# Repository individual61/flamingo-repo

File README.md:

FLAMINGO!

My festival buddy.My fave programs are the damped harmonic oscillator, the bouncing ball, and green fire. 

First iteration was a perfboard mess, second was a custom PCBA I designed and assembled. Currently runs off a small, flat USB power bank.

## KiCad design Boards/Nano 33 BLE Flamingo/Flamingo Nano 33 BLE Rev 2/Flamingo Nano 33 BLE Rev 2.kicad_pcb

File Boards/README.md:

This directory contains the board files.

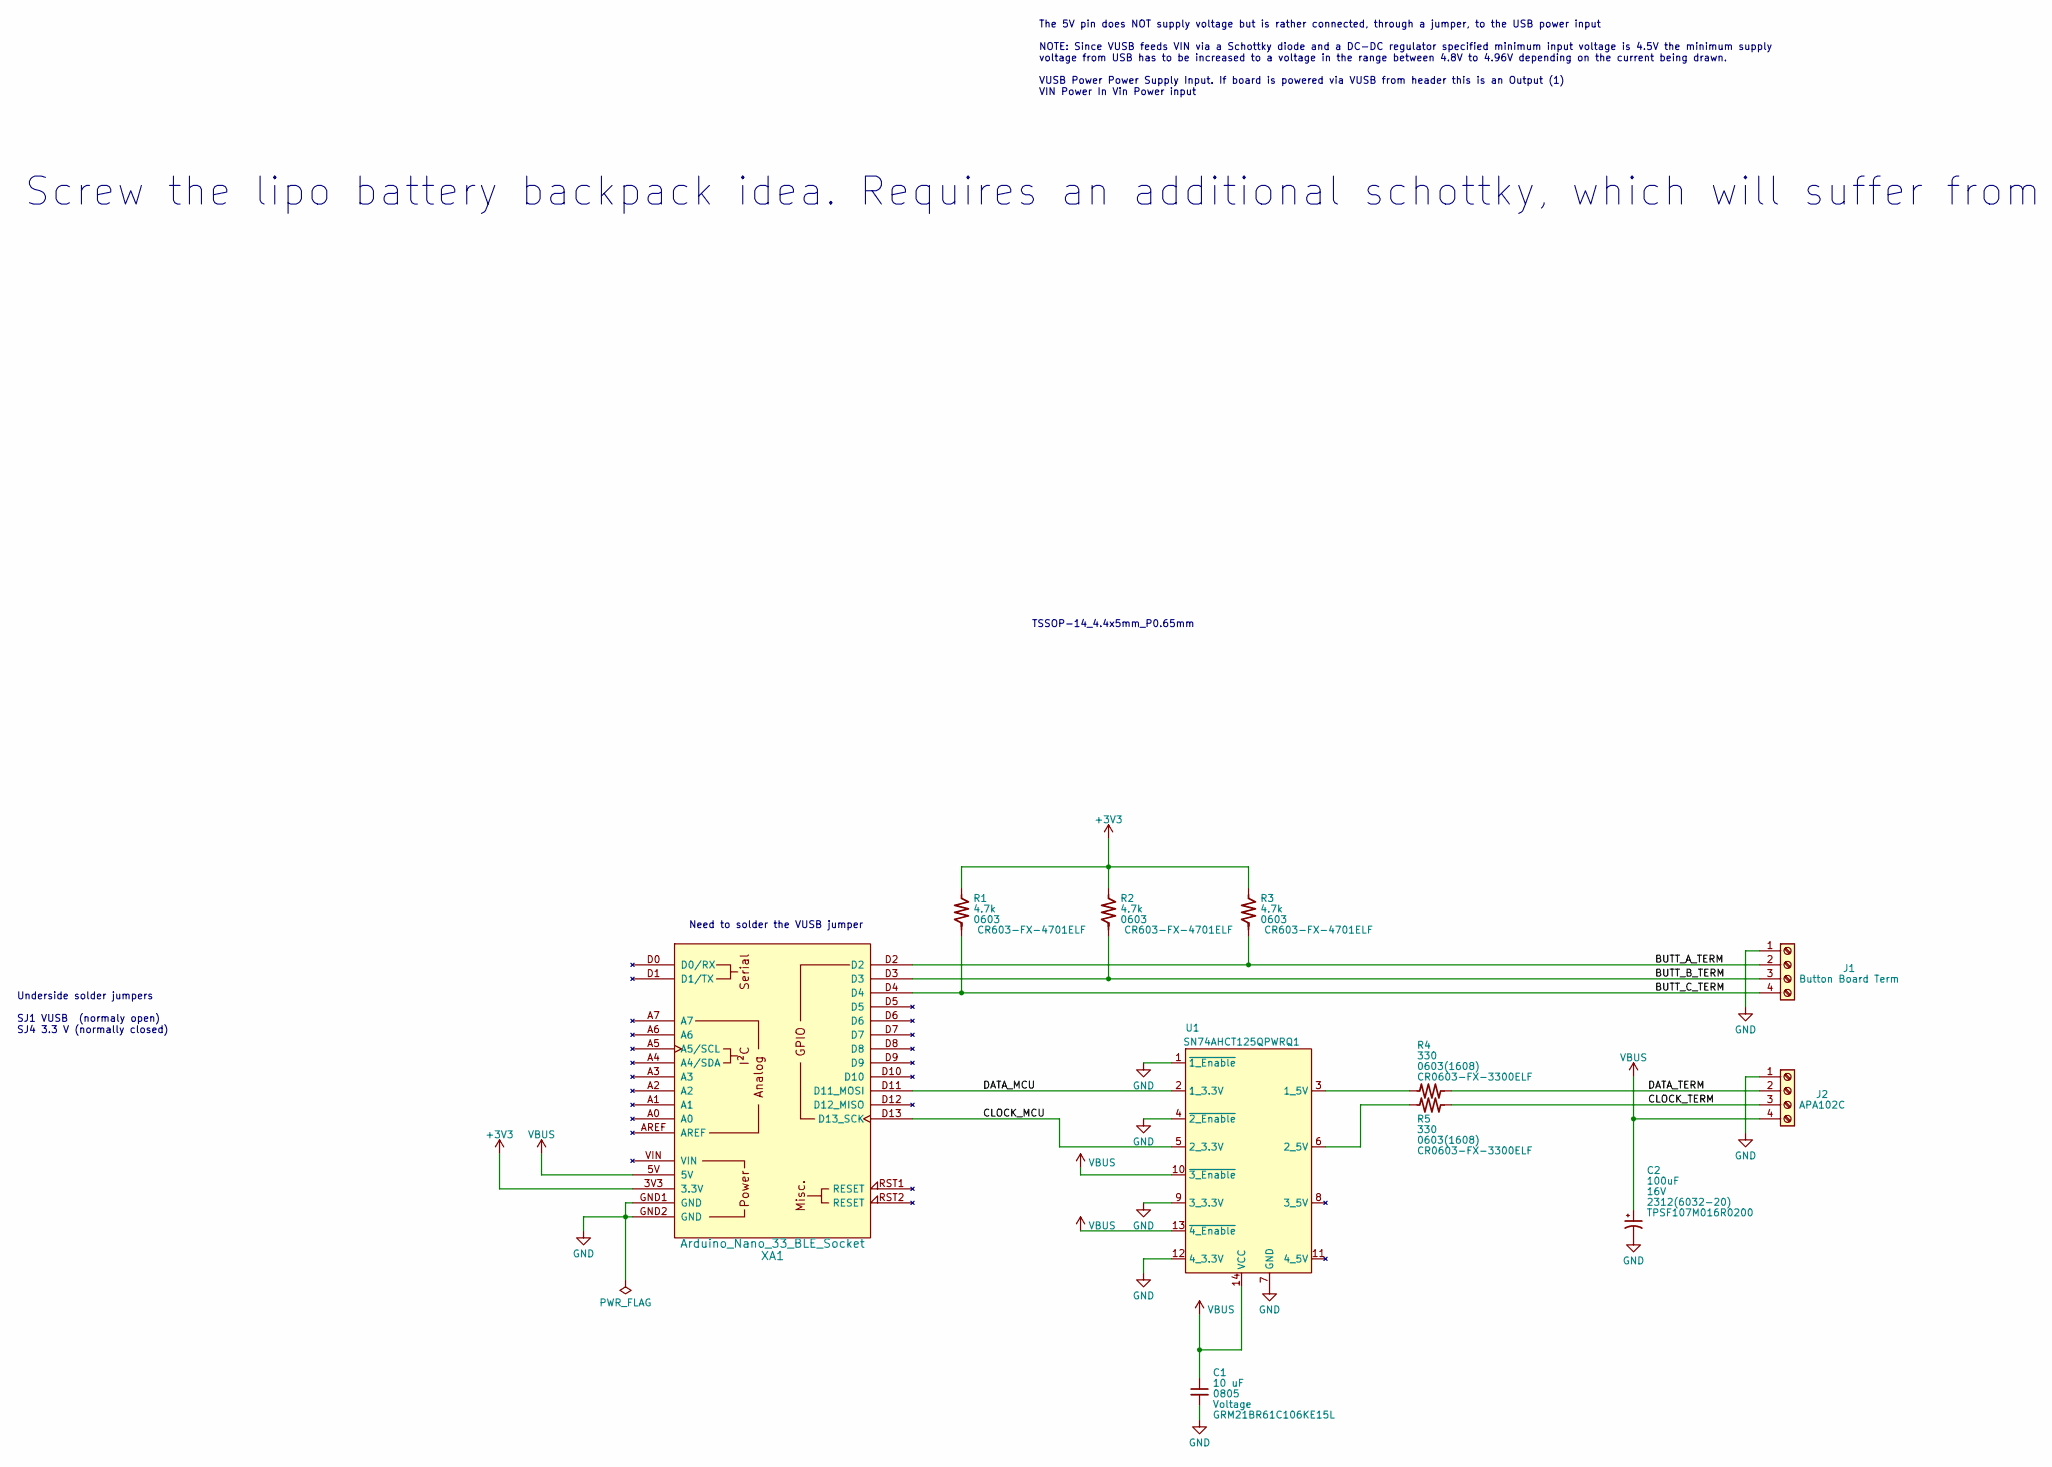
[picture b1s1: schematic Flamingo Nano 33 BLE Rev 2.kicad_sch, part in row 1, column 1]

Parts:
C1: 10 uF; C_0805_2012Metric_Pad1.18x1.45mm_HandSolder; Voltage Rating Voltage; MPN GRM21BR61C106KE15L
C2: 100uF; CP_EIA-6032-20_AVX-F_Pad2.25x2.35mm_HandSolder; Voltage Rating 16V; MFR P/N TPSF107M016R0200
J1: Button Board Term; TerminalBlock_TE_282834-4_1x04_P2.54mm_Horizontal; MFR PN 282834-4; DIGIKEY PN A98335-ND
J2: APA102C; TerminalBlock_TE_282834-4_1x04_P2.54mm_Horizontal; MFR PN 282834-4; DIGIKEY PN A98335-ND
R1, R2, R3: 4.7k; R_0603_1608Metric_Pad0.98x0.95mm_HandSolder; MPN CR603-FX-4701ELF; Digi-Key_PN 455-1719-ND
R4, R5: 330; R_0603_1608Metric_Pad0.98x0.95mm_HandSolder; MPN CR0603-FX-3300ELF
U1: SN74AHCT125QPWRQ1; TSSOP-14_4.4x5mm_P0.65mm
XA1: Arduino_Nano_33_BLE_Socket; Arduino_Nano_Every_Socket

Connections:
+3V3: R1.1, R2.1, R3.1, XA1.3V3 (3.3V)
/BUTT_A_TERM: J1.2, R3.2, XA1.D2
/BUTT_B_TERM: J1.3, R2.2, XA1.D3
/BUTT_C_TERM: J1.4, R1.2, XA1.D4
/CLOCK_MCU: U1.5 (2_3.3V), XA1.D13 (D13_SCK)
/CLOCK_TERM: J2.3, R5.2
/DATA_MCU: U1.2 (1_3.3V), XA1.D11 (D11_MOSI)
/DATA_TERM: J2.2, R4.2
GND: C1.2, C2.2, J1.1, J2.1, U1.1 (~1_Enable), U1.4 (~2_Enable), U1.7 (GND), U1.9 (3_3.3V), U1.12 (4_3.3V), XA1.GND1 (GND), XA1.GND2 (GND)
unnamed: R4.1, U1.3 (1_5V)
unnamed: R5.1, U1.6 (2_5V)
VBUS: C1.1, C2.1, J2.4, U1.10 (~3_Enable), U1.13 (~4_Enable), U1.14 (VCC), XA1.5V

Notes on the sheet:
Underside solder jumpers SJ1 VUSB (normaly open) SJ4 3.3 V (normally closed)
Screw the lipo battery backpack idea. Requires an additional schottky, which will suffer from Vf drop when running lights. Just use a USB power bank.
TSSOP-14_4.4x5mm_P0.65mm
The 5V pin does NOT supply voltage but is rather connected, through a jumper, to the USB power input NOTE: Since VUSB feeds VIN via a Schottky diode and a DC-DC regulator specified minimum input voltage is 4.5V the minimum supply voltage from USB has to be increased to a voltage in the range betwee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
Need to solder the VUSB jumper

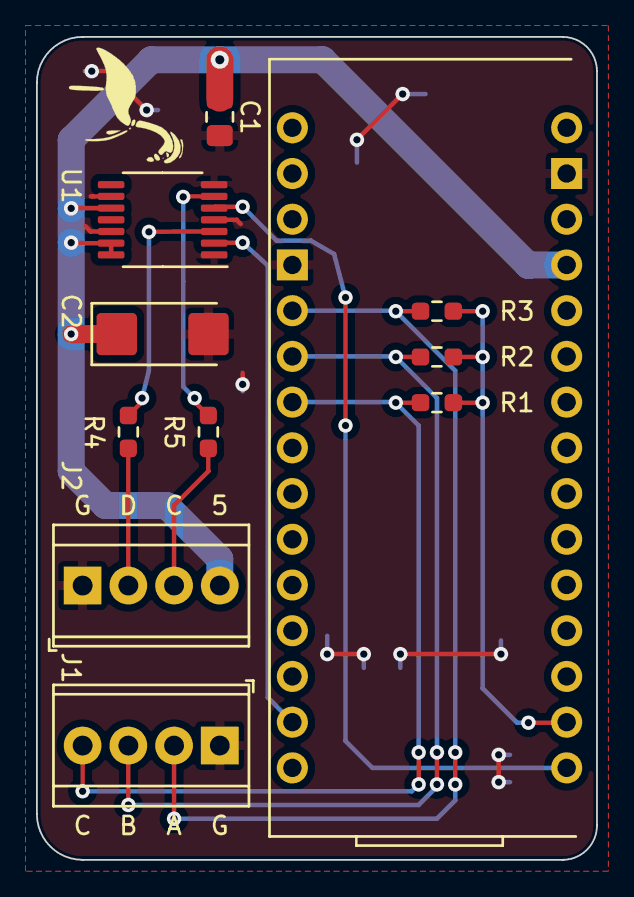
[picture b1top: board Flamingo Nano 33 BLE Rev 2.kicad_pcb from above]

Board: 2 copper layers, 31.1 x 45.7 mm, 11 parts (0 on the bottom side), 12 nets.

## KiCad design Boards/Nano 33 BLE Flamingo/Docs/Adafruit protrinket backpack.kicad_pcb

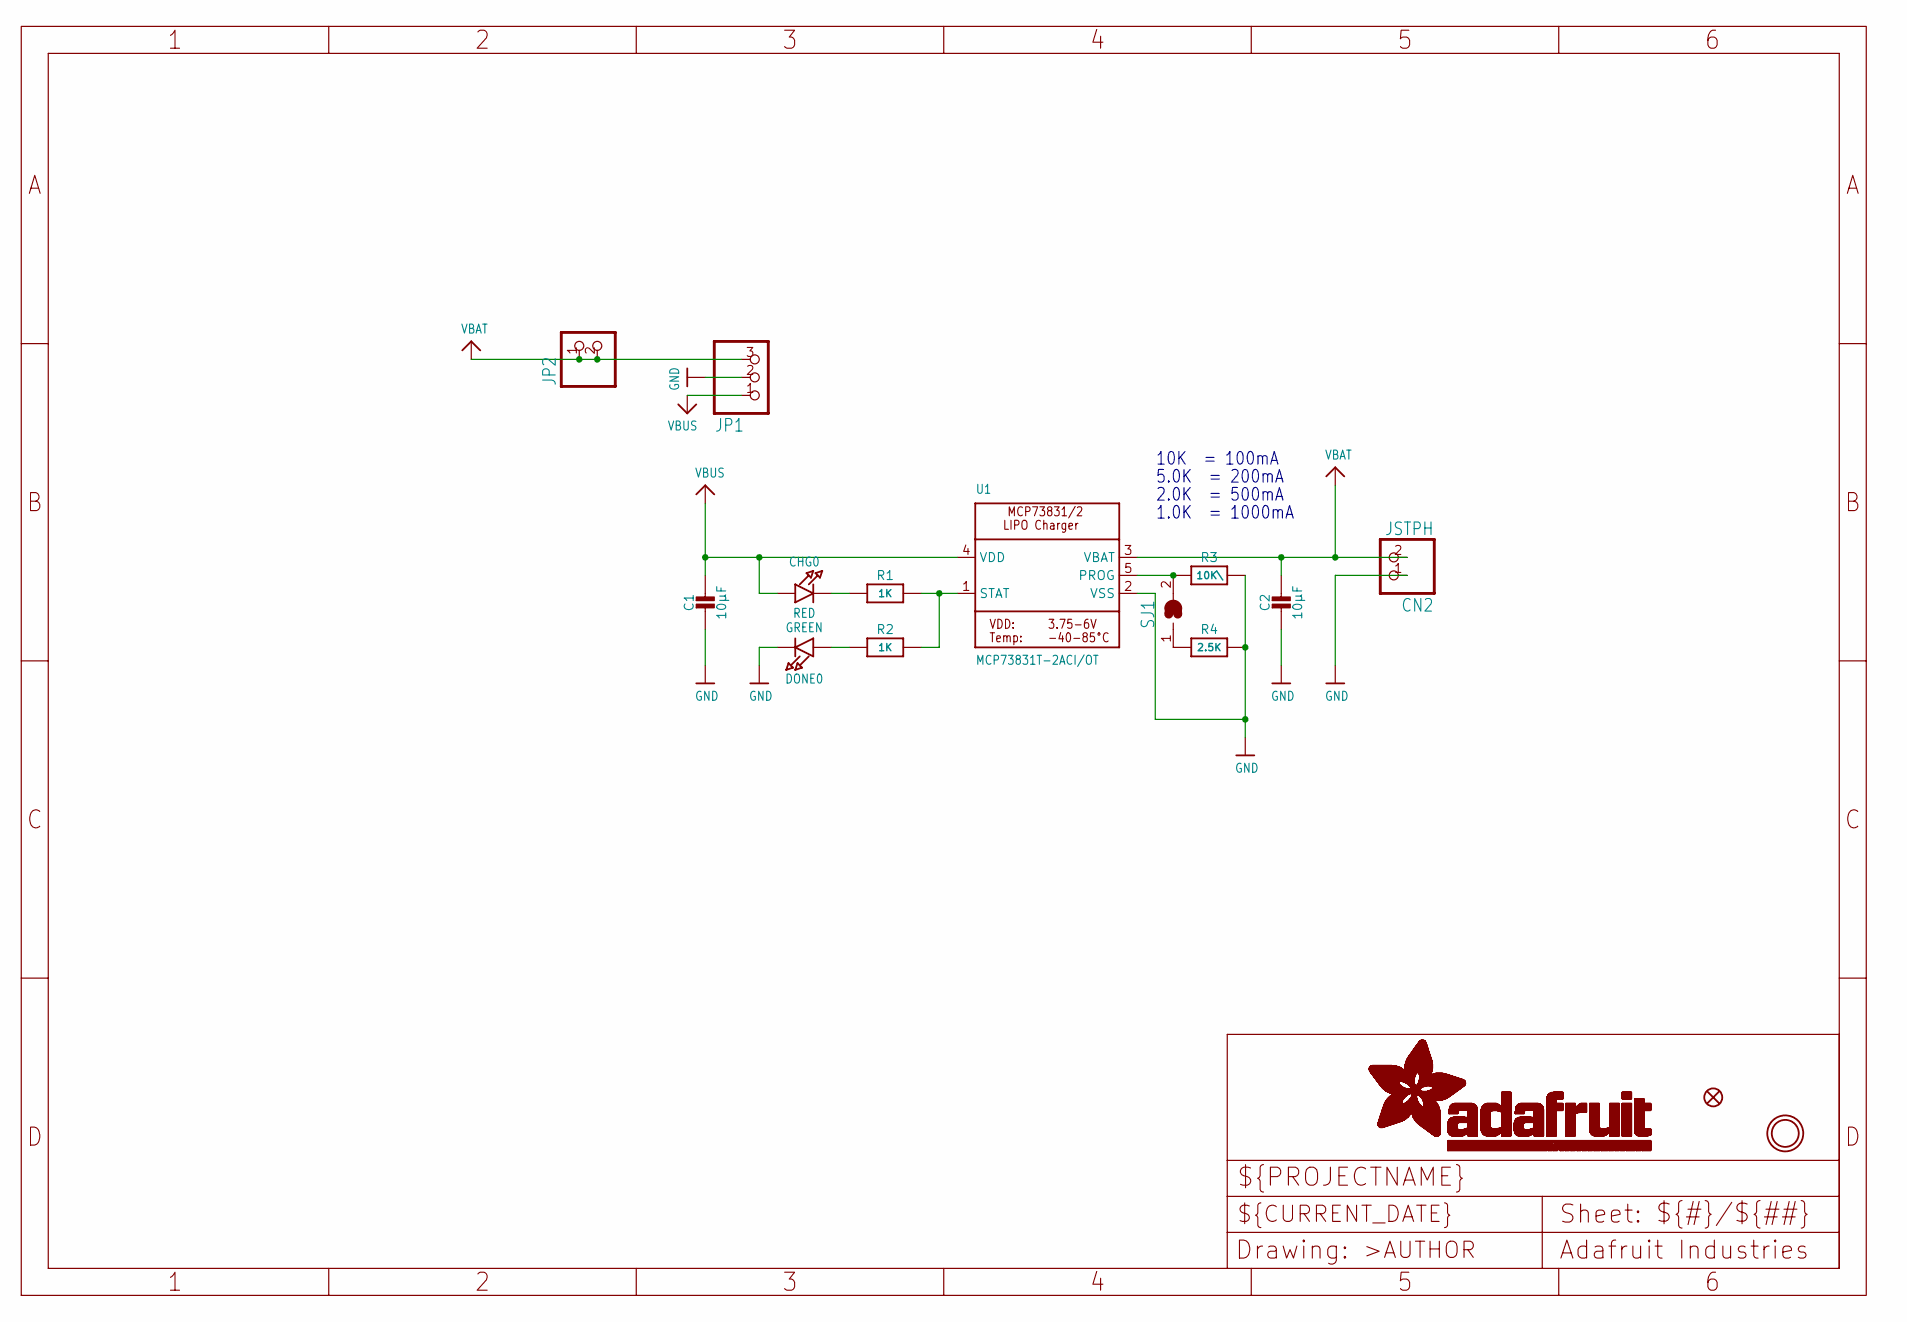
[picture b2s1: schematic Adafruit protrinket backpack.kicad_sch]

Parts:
C1, C2: 10µF; 0805-NO
CHG0: RED; CHIPLED_0805_NOOUTLINE
CN2: JSTPH; JSTPH2
DONE0: GREEN; CHIPLED_0805_NOOUTLINE
FID1: FIDUCIAL""; FIDUCIAL_1MM
JP1: HEADER-1X376MIL; 1X03_ROUND_76
JP2: HEADER-1X2ROUND; 1X02_ROUND
R1, R2: 1K; 0805-NO
R3: 10K\; _0805MP
R4: 2.5K; 0805-NO
SJ1: SOLDERJUMPER; SOLDERJUMPER_ARROW_NOPASTE
U1: MCP73831T-2ACI/OT; SOT23-5
U$10: MOUNTINGHOLE2.5; MOUNTINGHOLE_2.5_PLATED

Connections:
GND: C1.2, C2.2, CN2.1, DONE0.C, JP1.2, R3.2, R4.2, U1.2 (VSS)
unnamed: CHG0.C, R1.1
unnamed: R1.2, R2.2, U1.1 (STAT)
unnamed: R4.1, SJ1.1
unnamed: R3.1, SJ1.2, U1.5 (PROG)
unnamed: DONE0.A, R2.1
VBAT: C2.1, CN2.2, JP1.3, JP2.1, JP2.2, U1.3 (VBAT)
VBUS: C1.1, CHG0.A, JP1.1, U1.4 (VDD)

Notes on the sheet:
10K = 100mA
5.0K = 200mA
2.0K = 500mA
1.0K = 1000mA

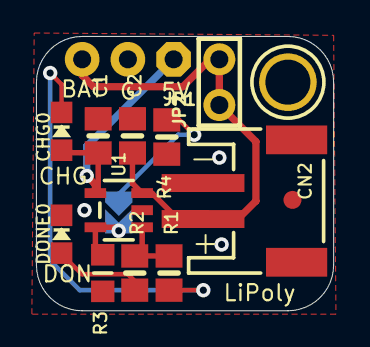
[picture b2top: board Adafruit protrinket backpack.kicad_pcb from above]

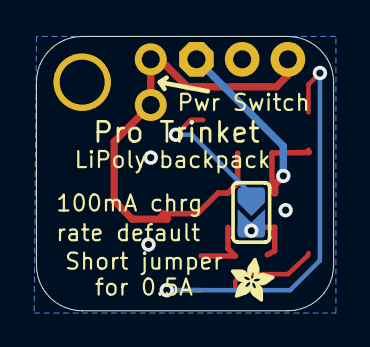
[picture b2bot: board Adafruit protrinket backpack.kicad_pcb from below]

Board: 2 copper layers, 16.5 x 15.2 mm, 16 parts (2 on the bottom side), 8 nets.

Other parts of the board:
U$9: ADAFRUIT_2.5MM

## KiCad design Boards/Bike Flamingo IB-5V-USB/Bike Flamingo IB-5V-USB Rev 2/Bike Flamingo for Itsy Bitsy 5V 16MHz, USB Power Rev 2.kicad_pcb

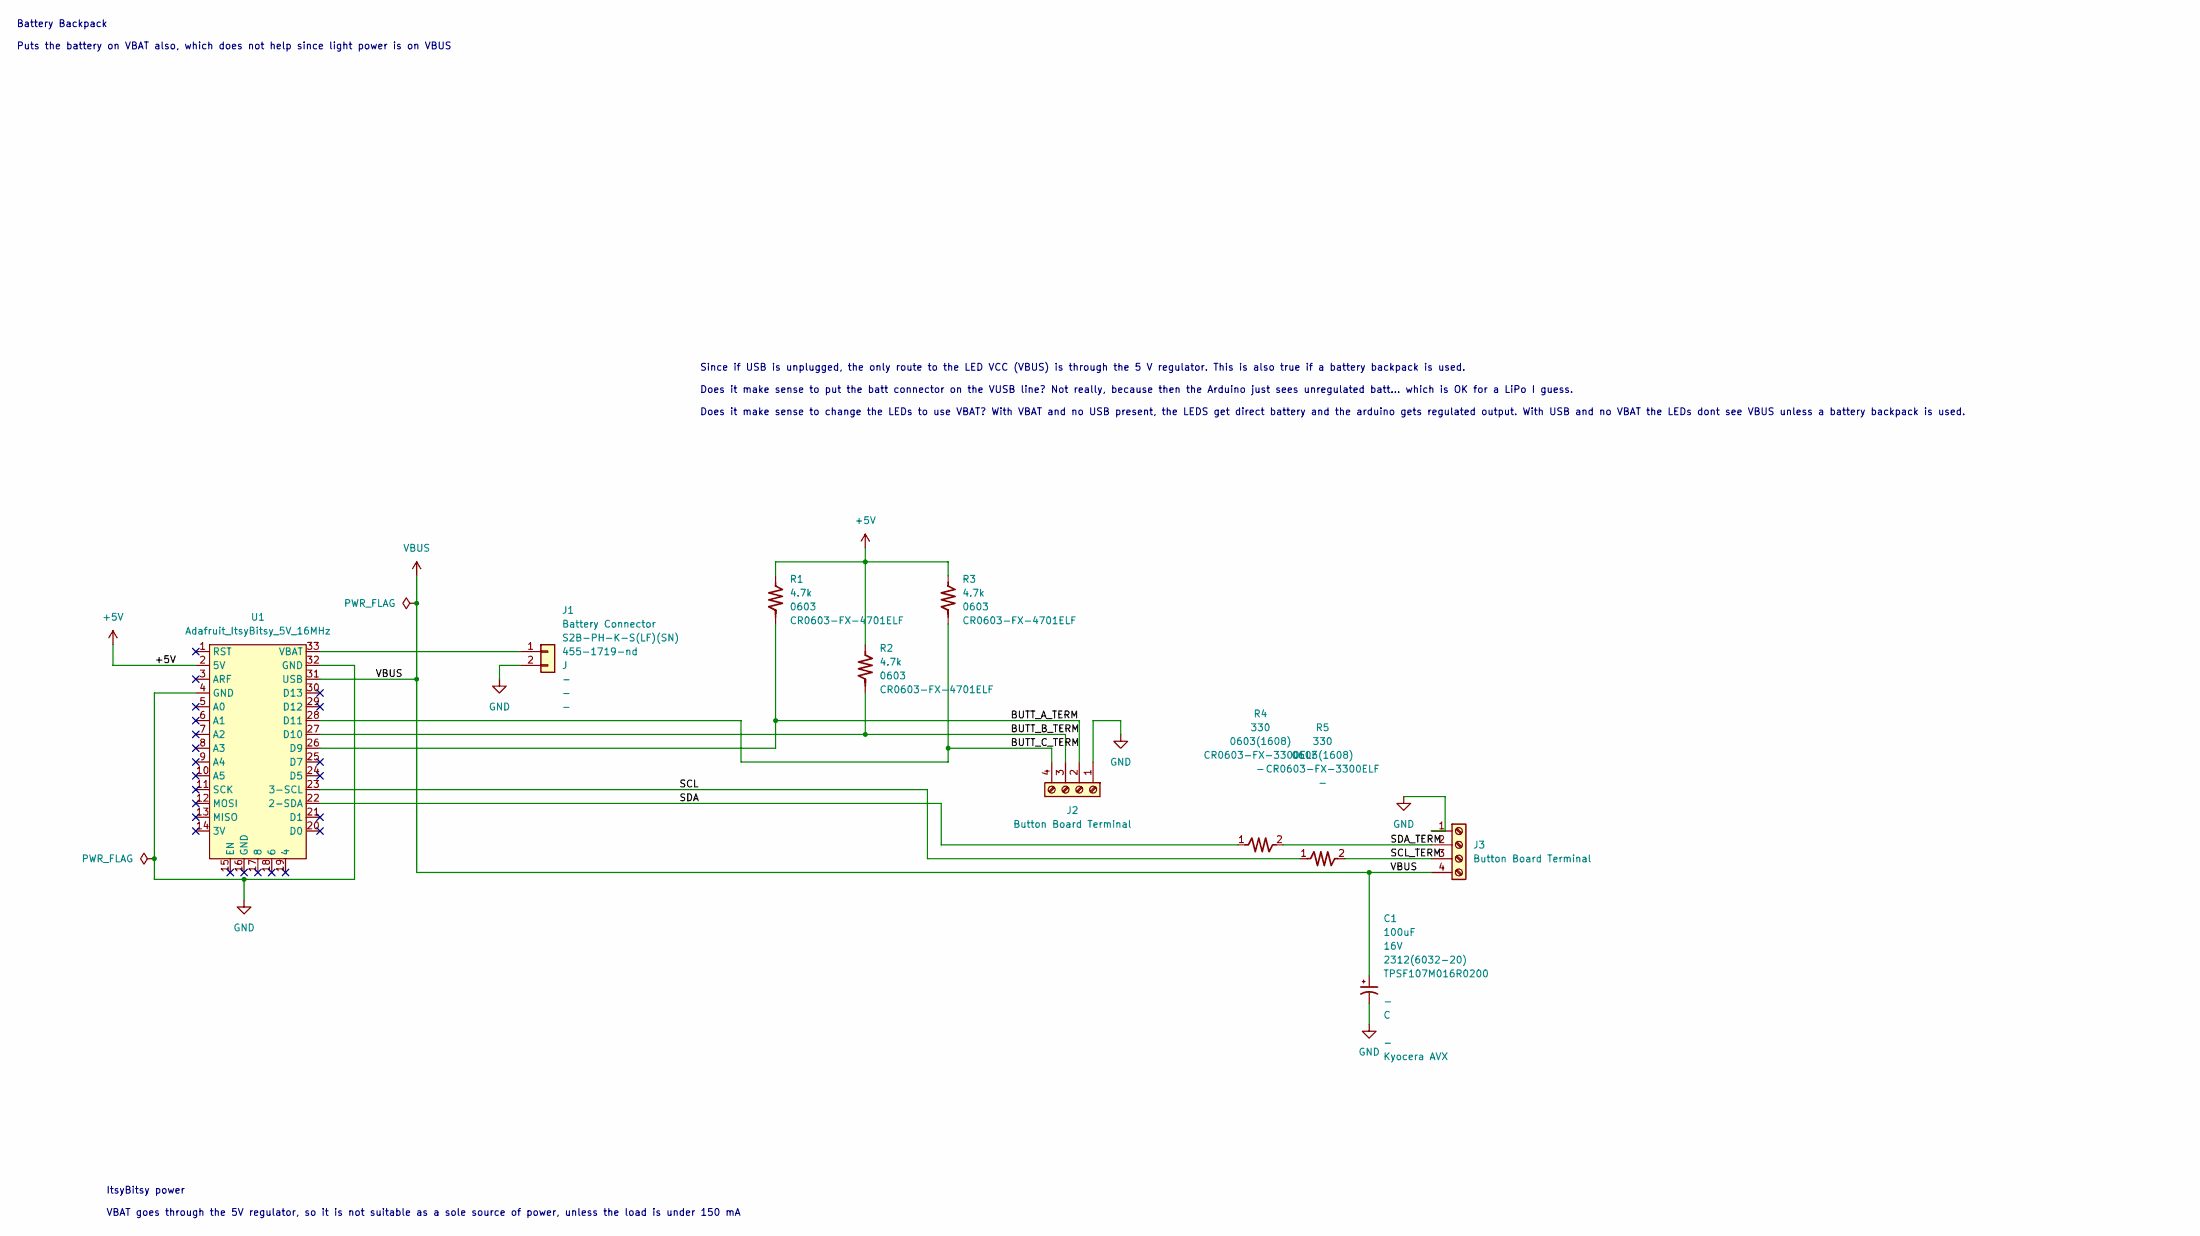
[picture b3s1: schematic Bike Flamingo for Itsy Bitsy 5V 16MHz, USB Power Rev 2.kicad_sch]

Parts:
C1: 100uF; CP_EIA-6032-28_Kemet-C_Pad2.25x2.35mm_HandSolder; Voltage Rating 16V; MFR P/N TPSF107M016R0200
J1: Battery Connector; JST_PH_S2B-PH-K_1x02_P2.00mm_Horizontal; MPN S2B-PH-K-S(LF)(SN); Digi-Key_PN 455-1719-nd
J2, J3: Button Board Terminal; TerminalBlock_TE_282834-4_1x04_P2.54mm_Horizontal; MFR PN 282834-4; DIGIKEY PN A98335-ND
R1, R2, R3: 4.7k; R_0603_1608Metric_Pad0.98x0.95mm_HandSolder; MPN CR0603-FX-4701ELF
R4, R5: 330; R_0603_1608Metric_Pad0.98x0.95mm_HandSolder; MPN CR0603-FX-3300ELF
U1: Adafruit_ItsyBitsy_5V_16MHz; Adafruit Itsy Bitsy 5V 16 MHz

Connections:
+5V: R1.1, R2.1, R3.1, U1.2 (5V)
/BUTT_A_TERM: J2.2, R1.2, U1.26 (D9)
/BUTT_B_TERM: J2.3, R2.2, U1.27 (D10)
/BUTT_C_TERM: J2.4, R3.2, U1.28 (D11)
/SCL: R5.1, U1.23 (3-SCL)
/SCL_TERM: J3.3, R5.2
/SDA: R4.1, U1.22 (2-SDA)
/SDA_TERM: J3.2, R4.2
GND: C1.2, J1.2, J2.1, J3.1, U1.4 (GND), U1.32 (GND)
unnamed: J1.1, U1.33 (VBAT)
VBUS: C1.1, J3.4, U1.31 (USB)

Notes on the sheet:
ItsyBitsy power VBAT goes through the 5V regulator, so it is not suitable as a sole source of power, unless the load is under 150 mA
Since if USB is unplugged, the only route to the LED VCC (VBUS) is through the 5 V regulator. This is also true if a battery backpack is used. Does it make sense to put the batt connector on the VUSB line? Not really, because then the Arduino just sees unregulated batt... which is OK for a LiPo I g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
Battery Backpack Puts the battery on VBAT also, which does not help since light power is on VBUS

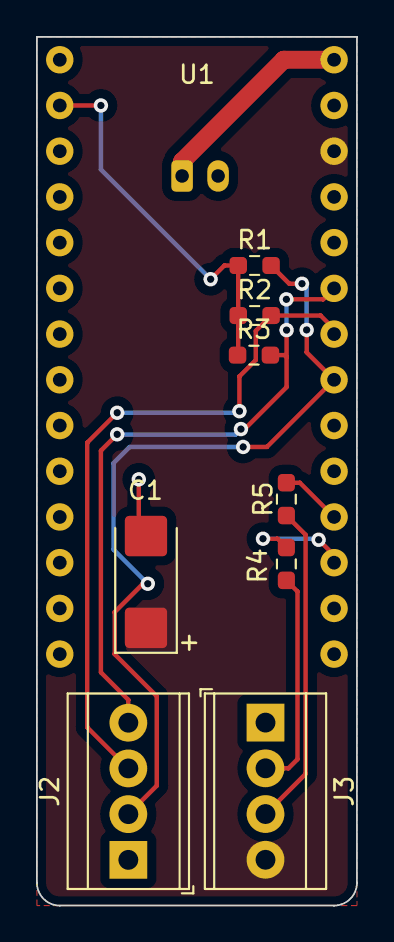
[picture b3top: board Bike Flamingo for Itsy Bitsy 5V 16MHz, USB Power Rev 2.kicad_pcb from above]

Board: 2 copper layers, 17.8 x 48.3 mm, 10 parts (1 on the bottom side), 11 nets.

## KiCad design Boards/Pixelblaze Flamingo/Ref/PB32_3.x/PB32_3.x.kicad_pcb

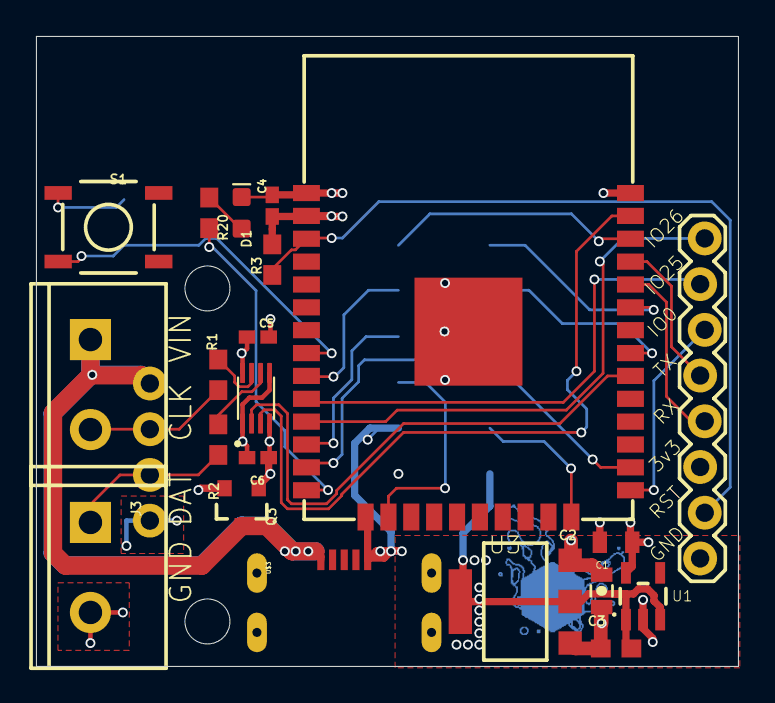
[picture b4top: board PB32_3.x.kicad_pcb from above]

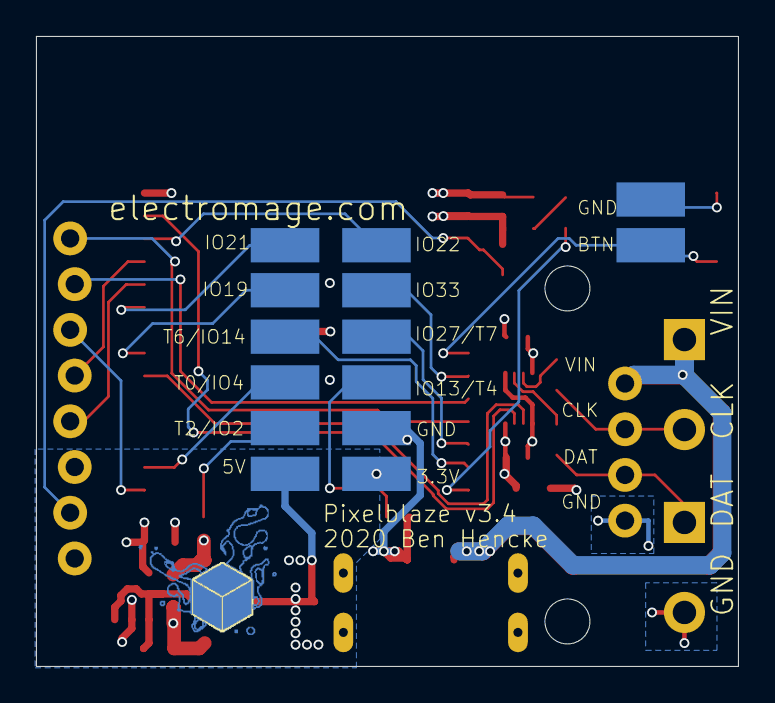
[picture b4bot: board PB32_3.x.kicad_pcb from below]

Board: 4 copper layers, 39.0 x 35.0 mm, 39 parts (15 on the bottom side), 29 nets.

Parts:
@HOLE0, @HOLE1: (no value)
C1: 1.0uF; 0805-CAP
C2: 10uF; 0805
C3: 4.7uF; 0603
C4, C5, C6: 0.1uF; C0402K
D1: LED-0603
GP1, GP3, GP6, GP8, GP9: PAD
IO2, IO4, IO13, IO14, IO19, IO21, IO22, IO27, IO33: PAD
J1: 1X08_LOCK
J2, J3: SCREWTERMINAL-5MM-2
J4: 1X04_NO_SILK
Q3: 2.5A/30V/105mΩ; SOT23-3
R1, R2, R20: 100; 0603
R3: 1k; 0603
S1: MOMENTARY-SWITCH-SPST-SMD-5.2MM; TACTILE_SWITCH_SMD_5.2MM
U1: AP2112K-3.3TRG1; SOT23-5
U2: ESP-WROOM-32
U3: NX1117C15Z; SOT223
U$1: SN74LVC2T45DCUR; SOP50P310X90-8N
U$2: ELECTRO_MAGE_PCB4_PIXEL_2#PNG
U$3: USB-CON-5PINUSB-SUNK-TIGHT; USB-SUNK-TIGHT

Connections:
+3V3: C2.1, C4.1, C6.1, GP1.P$1, J1.3, R3.2, U1.5, U2.2, U$1.1, U$1.5
+5V: C3.1, C5.1, GP6.P$1, U1.1, U1.3, U3.2, U3.4, U$1.8
BUTTON: GP8.P$1, S1.3, U2.8
EN: J1.2, R3.1, U2.3
GND: C1.2, C2.2, C3.2, C4.2, C5.2, C6.2, D1.C, GP3.P$1, GP9.P$1, J1.1, J3.2, J4.1, Q3.1, S1.1, U1.2, U2.1, U2.15, U2.38, U2.GND, U3.1, U$1.4, U$3.5
IO0: J1.6, U2.25
IO2: IO2.P$1, U2.24
IO4: IO4.P$1, U2.26
IO13: IO13.P$1, U2.16
IO14: IO14.P$1, U2.13
IO19: IO19.P$1, U2.31
IO21: IO21.P$1, U2.33
IO22: IO22.P$1, U2.36
IO25: J1.7, U2.10
IO26: J1.8, U2.11
IO27: IO27.P$1, U2.12
IO33: IO33.P$1, U2.9
LED: R20.2, U2.14
MOSI: U2.37, U$1.3
MOSI_OUT: J3.1, J4.2, R2.2
unnamed: C1.1, Q3.2, U3.3
unnamed: R1.1, U$1.7
unnamed: R2.1, U$1.6
unnamed: D1.A, R20.1
RX: J1.4, U2.34
SCK: U2.30, U$1.2
SCK_OUT: J2.2, J4.3, R1.2
TX: J1.5, U2.35
VIN: J2.1, J4.4, Q3.3, U$3.1

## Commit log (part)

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2017-04-27 Initial Commit
    Created folder and file structure.
2017-04-27 Initialized Platformio for Flamingo Original
    Turned Platformio back on, which created two new files.
    The code compiles.
2017-04-27 Created Code/Flamingo Rev B
    Copied from Flamingo Original
2017-05-06 Refactored to multiple files
    Refactored the code into multiple files. There is a parameters.h for
    preprocessor definitions and extern variable declarations.
    loop() is now a hell of a lot tidier, as it should be.
    Compiles, but not tested.
2017-05-06 Move variables to PP defs, debug crashing
    Tidied up code, started addressing why the board built for BM 2016
    crashes. Added freeRAM() to diagnose. Consistently crashes when it
    reaches DHO_Sinetripes(). At that point free SRAM is around 147, and
    then I try to load a huge float table.
    Committing before trying to reduce the memory requirements of this
    program.
2017-05-06 Putting big things in PROGMEM
    Found why it was crashing. Free SRAM was 147 before moving a huge float
    table to PROGMEM and changing floats to ints (later dividing by 100.0),
    plus another PROGMEM change. I also put all setup() Serial strings in
    F().
    After all these changes, free SRAM is at 927!
2017-05-07 A few more PP refs and F()
    Moved a few more variables to PP defs and strings into F().
    Open issue: the blob program’s values follow the blob shape but
    flicker, therefore the array is not being read correctly from PROGMEM.
2017-05-07 Applied clang-format, tidied code
    Got clang-format config as I want it, and tidied up effects.cpp
2017-05-08 Added Sparkle/-Pink/-Fizz
    Added three programs.
    Sparkle: sparkles.
    Sparkle Pink: Sparkles pink.
    Sparke Pink Fizz: Reacts to acceleration and sparkles more. Needs
    adjustment.
    Also added some code to make single-pixel programs have their
2017-05-08 Added rolling time average (incomplete)
    Added a rolling time average. Needs better decay.
2017-05-09 SparkleFizz now works properly
    However, the exp() function slows things down a lot.
    Also, what I’m really looking for is jerk, not acceleration.
    Also, might address whole strand and not just one third of it.
2017-05-09 Trying to understand behavior of SparkleFizz
    SparkleFizz does not change gracefully from short to long random
    intervals. The issue seems to be with random(0, MAX) giving only 0 and
    MAX and nothing in between.
2017-05-10 Continued work on Sparkle Fizz
    The issue is that for max acceleration greater than MAX_G_SPARKLEFIZZ,
    it takes a while for acc_decayed to be equal to MAX_G_SPARKLEFIZZ. If
    acc_max is twice MAX_G_SPARKLEFIZZ, half of ACC_MAX_DECAY_RATE is spent
    at solid sparkle, leaving only the other half to get down to zero (for
    a linear decay).
    What’s needed is a separate decay timescale that starts at that moment,
2017-05-11 Increased SparkleFizz decay period to 16 s
    16 seconds and 2 g threshold seem to work well.
    Currently figuring out how to get a representative average of the
    acceleration derivative.
2017-05-12 Changed SparkleFizz rate to 20 seconds
    Looks better.
    At this point I’d say this program is “good enough”. The derivative of
    acceleration will have to wait. I’m not convinced it will be much of an
    improvement. Picking a derivative interval doesn’t seem
    straightforward.
    On to new programs.
2017-05-12 Tidied up code for merge back into master branch
2017-05-12 Created Physical version of DHO
    Finally revisited the DHO and acceleration equations. This allowed me
    to use the acceleration value in m/sˆ2 and ultimately express the ball
    position as a value centered on 0.0 when upright and -2.0 when upside
    down—exactly as one would expect for a mass on a spring at rest at x =
    0.0.
    This also allows me to change m, k and c without having to rescale
2017-05-13 Fixed accel functions: now really physical
    Found I had used acc_now instead of m*a in the integration of the
    equation of motion.
    getBallPosition() now returns 0 when upright and -2.0 when inverted, no
    matter what parameters are chosen for m, k and c.
    Parameters might need a little tweaking.
2017-05-13 Small tweaks for physical DHO
2017-05-15 Worked on DHO Fade and Comet; added utils.cpp/h
    Both DHO Fade and Comet are unsatisfactory. Fade has gaps when the ball
    moves too fast to register on all pixels, and Comet doesn’t seem to
    display the trail, no matter how long I make the history.
    Added utils.cpp/h for stuff like freeRam().
    Renamed setPixelByIndex to setPixelByStrandIndex for clarity.
    Added fadeWholeStrip(float fade_coef) and void
2017-05-20 Timing getballposition()
    Nope, not the cause of the delay. So is it the Dotstar library?
2017-05-20 DHO_Fade() is only 7 ms period, yet has gaps
    Will FastLED help? fadeWholeStrip() was the biggest contributor, at 7
    ms.
2017-05-22 First pass, untested, compiles
    As described. Likely nothing will work.
2017-05-22 FastLED transition cleanup continues
    My LED color order was wrong, so Flamingo pink looked too blue. Now
    things are as they should be. DHO_Comet is not working but I’m not too
    tied to it anyway. Can probably be fixed easily.
2017-05-22 Changed random() to random8/16()
    Also removed any mention of Adafruit Dotstar library
2017-05-23 Created programs/ dir
    effects.cpp was getting too long. Created programs-common.h and .cpp
    Transition to FastLED() is complete, save for some tweaks and
    adaptation.
2017-05-23 Added sparks to Fire With Palette
    Not bad at all:
    // No more than N sparks at a time, N could be around 5
    // Created with low probability every frame
    // Sparks ascend at constant different and random rate (found to be
    best to go 2 and 3 pixels per frame)
    // Sparks can die before reaching the top. They are born with "pixels
2017-05-24 Added Bouncing Balls. Totally does not work.
2017-05-24 Bouncing balls still not working
    Each ball is slower than the next. Need to check how timing intervals
    for RK are set.
2017-05-25 Bouncing Ball works. Code cleanup.
    Got BB to work, sort of. One ball looks better than more.
    Cleaning up programs for LiB.
2017-05-25 Added rainbow.cpp; pre-release for LIB2017
    Changed to FastLED’s rainbow functions. Used them in DHO Rainbow.
    Kept original fire because it has more yellow than a rgb -> grb swapped
    pallette fire. Added sparks to it. Added pink fire. Added rainbow fire.
    OMG.
2017-05-25 Initial totem testing
    Cleanup, F() macros, return if stolen intro.
2017-05-25 Small fixes for Totem
    Totem’s accelerometer is upside down. That explains A LOT.
2017-05-26 Added RUN_ON_TOTEM switch
    Switches between the accelerometer calibration of the testbed or the
    Totem.
2017-05-26 Made fire rainbow slowly cycle pallette.
    my god it’s full of stars
2017-05-26 Release candidate for LiB 2017
    Set acc cal for Totem.
2017-07-27 Added components to schematic
    Nothing connected to nets yet.
2017-07-29 Completed preliminary component layout
    Decided to just glue the 5 wires from the remote and 4 for the lights
    to the underside of the PCB.
2017-08-24 Changes for bike strip
    Made changes so it can be used on the bike. Fire is too slow, no time
    to fix.
2018-01-13 Probably moving away from Eagle...
    This may be the last commit with Eagle files
2018-02-05 Starting to create Rev 2
2018-02-06 First pass of battery charging section complete
    Still needs another pass for component and value selection.
2020-10-03 Adding first sub-sheets
    Arduino
    Battery Charger
    IMU
    Power
2020-10-07 PCB: bringing in symbols, re-making battery charger sheet, still has todo
2020-10-08 Advanced schematic for battery charger
    To do:
    * Find a better connector for the switch than a JST PH2
    * Check the polarity of the battery connector w.r.t. Adafruit batteries.
    *Assign footprints
2020-10-08 Fixed footprint libraries to v5, added some footprints
2020-10-09 Worked on Power board mainly.
    Still have to resolve the power sharing.
2020-10-10 NOSTUFF 5V LDO bc not needed. Added Sch diode on 5v LDO.
2020-10-12 Moved Battery Charger sheet into Power sheet
    Right before addition of power sharing mosfet, maybe
2020-10-13 More work on Arduino schematic, created button board schematic
    Button board schematic should probably be a separate project
2020-10-13 More work on Arduino sheet
    Added V_BUS sensing, removed V_BAT sensing bc it would be a discharge situation. Assigned some lines to pins. Added placeholders for headers.
2020-10-13 Tidy up
2020-10-18 Added Button Remote project
2022-05-20 Undocumented changes
2022-05-20 Created through hole files, did not do anything
2022-05-25 Fixed compilation issue by copying I2Cdevlib files into lib/ and discovered rewrite is very incomplete womp womp
    https://community.platformio.org/t/library-header-not-found-installed-library-seems-to-be-empty/27841/5
2022-05-25 It finally builds. Turns out going with main branch instead of dev was a bad idea. Or something
    Fixed it by copy pasting in code that seems to have been accidentally nuked, harmonic_oscillator.cpp.
2022-05-25 A commit just to get things synced with .gitignore
2022-08-01 Got interrupts on all 3 butotns worksing
2022-08-01 Re-adding Bike Flamingo after wiping repository due to broken stash
2022-08-01 Testing lights
2022-08-01 Sparkles work great
2022-08-02 Started creating carrier board schematic for Bike Flamingo
2022-08-02 Finished Bike Flamingo board Rev 1
2022-08-03 As ordered from JCLPCB with generated gerbers
2022-08-03 Got the skeleton of a good architecture, start to migrate/merge w Flamingo
    Have 3 buttons with ISR, program index, demonstrated sparkle and rainbow cycle fire.
    Time to merge and generalize code.
2022-08-03 Finally got brightness array to pass compile
2022-08-03 First successful compilatiion after bringing legacy code into bike flamingo
2022-08-03 Found the memory corruption location, will have to adapt to arbitrary number of strands
    The issue is here
    void setPixelByStrandIndex(uint16_t index, CRGB color)
    {
    if ((index >= 0) && (index < NUMPERSTRAND))
    {
    // index goes from 0 to NUMPERSTRAND - 1
2022-08-03 Fixed the bug with the memory corruption, commented out a lot of print statements
2022-08-04 Added some notes on power: the battery connector is not likely to be useful
    Since if USB is unplugged, the only route to the LED VCC (VBUS) is through the 5 V regulator. This is also true if a battery backpack is used.
    Does it make sense to put the batt connector on the VUSB line? Not really, because then the Arduino just sees unregulated batt... which is OK for a LiPo I guess.
    Does it make sense to change the LEDs to use VBAT? With VBAT and no USB present, the LEDS get direct battery and the arduino gets regulated output. With USB and no VBAT the LEDs dont see VBUS unless 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
2022-08-11 Found issues with Rev 1 Bike Flamingo, made Rev 2, added time()
2022-09-20 Last commit before switching to Pixelblaze
    When a better solution comes along, you have to be able to switch, even if it means not using months and months of your own work...
2023-04-28 Carrier board for Arduino Nano 33 BLE Rev 2 sent to fab
2023-05-03 Started from scratch. Buttons and timing working.
2023-05-04 Damped Harmonic Oscillator is working
    Found good settings for 120 BPM bounce. Also fixed the ball being waaaay far out when it is first run, caused by the timing interval not being updated during setup()
2023-05-07 A little more advancement on harmonic oscillator, beginnings of a program structure, etc
2023-05-08 Removed while(!Serial), prevented loop start until connected to apparently
2023-05-09 Implemented Sparkle
2023-05-16 A mess, but first working version of Fire Green Original
2023-05-17 Completed first successful Rainbow Fire
2023-05-17 Converted Synchronized Random Numbers Pixelblaze program
2023-05-17 Completed several Sync Rand Num settings
2023-05-19 Added compass (inop) and gflash
2023-05-23 Finished adjusting max brightness for all programs
2023-05-23 Finished brightness calibration for max current and levels
2023-05-25 measured two batteries on max burn with this code
2023-05-26 As taken to LIB 2023!
2023-05-30 todo
